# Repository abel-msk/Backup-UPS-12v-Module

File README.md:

# Backup UPS 12V Module

English | [Русский](readme.ru.md)

No-break switchover between a 12 V PSU and a 3S2P battery, with load current up to 8 A. Board size,
mounting holes and connectors J1, J4, J6, J7, J8 match the Backup power switch 12v Module.

## Background

This board is the next step of the [Backup power switch 12v Module](https://github.com/abel-msk/Backup-power-switch-12v-Module) project (v5.0). It keeps the board outline and the main connectors, but the switchover and the charger were redesigned because of the limitations found in v5.0:

| | Backup power switch v5.0 | Why it was changed | This board |
|---|---|---|---|
| **Switchover** | Relay K1 controlled by ESP32-C3 firmware, diode-OR D7 holds the outputs while the relay moves | Backup depended on running firmware, and the relay is a mechanical part in the 12 V path | Two ideal diodes and no relay. The battery leg is enabled by hardware, without firmware |
| **Mains loss detection** | Firmware compares INA219 currents | The battery back-feeds the PSU side through D7 and K1, so the PSU voltage divider still reads close to normal | U1 blocks back-feed, and the U7 detector measures PSU_IN directly |
| **Charging** | CN3763 buck charger fed directly from the PSU | With a 12.6 V PSU the pack reaches only about 11.2–11.4 V (45–55 % capacity), DONE is never asserted and most BMS boards do not balance | MT3608 boosts the charger input to 14.7 V, so the pack can charge to 12.6 V |
| **Monitoring** | Two INA219 sensors and ADC dividers | No longer needed to detect mains loss | Mains loss is detected in hardware, without a sensor. U8 (INA226) on shunt R29 measures the output current and voltage for monitoring only. The ESP32-C3 also reads ON_BATTERY, CHRG_SIG and DONE_SIG |

This design has not been tested on hardware yet.

## How it works

- **PSU to output:** ideal diode U1 (LM74700-Q1) + Q1 (AOD514).
- **Battery to output:** U2 + Q2. While mains is present, Q3 holds the EN pin of U2 low, so the battery does not discharge.
- **Mains detector:** reference U7 (LMV431AIMF) and switch Q10 (AO3401A) drive the bases of Q3 and Q7. The threshold is set with RV1.
- **Mains lost:** current immediately flows through the body diode of Q2, then U2 turns Q2 on. The output does not drop out.
- **Charging:** the MT3608 boosts PSU_IN to 14.7 V, and the CN3763 charges the pack to 12.6 V at 0.8 A.
  Without the boost, a buck charger running from 12 V cannot fully charge a 3S pack (see the README of the old board).

## Switchover logic

The thresholds and timings below come from calculation and ngspice simulation. They have not been measured on hardware.

The power path is two ideal diodes feeding the common node VOR. The no-break behavior comes from the body diode of Q2: it is permanently connected from the battery to VOR and starts conducting on its own, with no control signal. The detector only decides when to turn Q2 fully on.

### How the detector works

U7 compares the voltage on REF with its internal 1.24 V reference. REF receives a fraction of PSU_IN through the divider R20 + RV1 (upper leg) and R21 (lower leg).

| PSU_IN | U7 | Q10 | Q3 and Q7 | BAT_EN (U2 EN input) | Q2 | ON_BATTERY |
|---|---|---|---|---|---|---|
| above threshold | conducting | on | on | about 0 V | off, only the body diode conducts | 0 |
| below threshold | off | off | off | pulled up through R3 from SW_ON | on | 1 |

When PSU_IN is above the threshold, U7 pulls the gate of Q10 down through R24. Q10 turns on and feeds the bases of Q3 and Q7 through R1. When PSU_IN is below the threshold, R23 turns Q10 off and R2 discharges the bases.

### Why there are two thresholds

Without hysteresis, the detector would chatter around the threshold because of ripple on PSU_IN. The hysteresis comes from R22 (10 MΩ) between the drain of Q10 and REF:

- **Q10 on (mains present):** R22 is in parallel with the upper leg and raises REF slightly. PSU_IN has to fall further before U7 turns off. This is the battery enable threshold: `1.24 × (1 + (R20 + RV1) ∥ R22 / R21)`.
- **Q10 off (running on battery):** R22, through R1, loads the lower leg and lowers REF slightly. PSU_IN has to rise further before U7 turns on. This is the battery disable threshold: `1.24 × (1 + (R20 + RV1) / (R21 ∥ (R22 + R1)))`.

Temperature from 0 to 60 °C shifts the threshold by about ±0.02 V, because the threshold is set by the U7 reference and not by a transistor base-emitter voltage.

| RV1 | Battery enabled when PSU_IN falls below | Battery disabled when PSU_IN rises above |
|---|---|---|
| 0 Ω | 10.96 V | 11.15 V |
| 5 kΩ | 11.26 V | 11.46 V |
| 10 kΩ | 11.56 V | 11.77 V |

With tolerances (Vref ±1%, R20 and R21 ±1%, RV1 ±10%, others ±5%, 0–60 °C):

| RV1 | Battery enable | Battery disable |
|---|---|---|
| 0 Ω | 10.72–11.18 V | 10.92–11.38 V |
| 10 kΩ | 11.31–11.87 V | 11.52–12.09 V |

Hysteresis is 0.18–0.23 V. Turning RV1 clockwise raises the threshold (per the Bourns 3296 datasheet; confirm on the Baoter part with a continuity check).

### Mains lost

1. PSU_IN falls and VOR falls with it. C5 supplies part of the current.
2. As soon as VOR is above PSU_IN, U1 turns Q1 off. The battery does not back-feed the PSU or the MT3608.
3. When VOR drops about 0.8 V below the pack voltage, the body diode of Q2 starts conducting. From this point the battery supplies the load.
4. PSU_IN crosses the battery enable threshold. U7, Q10, Q3 and Q7 turn off.
5. About 60–80 µs after the threshold crossing, BAT_EN rises through R3. U2 turns Q2 on, and the drop falls from 0.8 V to a fraction of a volt.
6. ON_BATTERY goes to 1, and D4 and the external BAT LED on J12 light up.

The duration of steps 3–5 depends on how fast PSU_IN decays. If the pack is discharged so far that its voltage minus 0.8 V is below the threshold, the detector acts before the diode conducts and this phase does not occur.

### Mains restored

1. PSU_IN rises and crosses the battery disable threshold. U7 and Q10 turn on, Q3 pulls BAT_EN to ground in about 9 µs, and Q2 turns off. The load stays on the body diode of Q2.
2. When PSU_IN exceeds VOR, U1 turns Q1 on and the load moves to mains with no break.
3. ON_BATTERY returns to 0, and the CN3763 charges the pack again.

### Short dips

C3 and R2, together with the switching delay, reject short disturbances. The detector ignores a PSU_IN dip from 12.6 to 9 V lasting up to 50 µs, and a dip of 100 µs or longer enables the battery. When that happens the battery simply picks up the load.

### Output switch

The BAT_EN pull-up comes from SW_ON, so with J10 open U2 stays disabled regardless of the detector. Q5 then disconnects the output, and the ESP32 and the indicators turn off along with VOUT.

### Limitations

- **Sustained PSU sag.** If PSU_IN stays between the threshold and the pack voltage minus 0.8 V (full pack: from the threshold up to 11.8 V), the battery is not yet enabled, but current flows through the body diode of Q2. That is about 6.4 W at 8 A, so this state must not be sustained.
- **PSU voltage.** The battery disable threshold must be at least 0.3 V below PSU_IN under load. Do not use the top position of RV1 with a 12.0 V PSU.
- **Full pack with a 12.0 V PSU.** The body diode of Q2 is close to conducting, so the battery can discharge slightly. Set the PSU to 12.3–12.6 V.

## Schematic sheets

| Sheet | File | Contents | Connections to root |
|---|---|---|---|
| Root | `Backup UPS 12v Module.kicad_sch` | ideal diodes, output switch, ESP32, status transistors Q8 and Q9, indicators, J11 and J12 | |
| Boost | `boost.kicad_sch` | MT3608 (U3) and its components | PSU_IN, V15 |
| Charger | `charger.kicad_sch` | CN3763 (U4) and its components | V15, BAT+, CHRG, DONE |
| Detector | `detector.kicad_sch` | mains detector: threshold (U7, RV1, R20–R22), Q10, Q3, Q7 | PSU_IN, SW_ON, 3V3, BAT_EN, ON_BATTERY |

## ESP32-C3 Pro Mini

3.3 V comes from an AMS1117-3.3 (U6) fed by VOUT, so the ESP turns off when the output is switched off.

| GPIO | Signal | Meaning |
|---|---|---|
| GPIO4 | ON_BATTERY | 1 on battery, 0 on mains. Interrupt on both edges = switchover moment |
| GPIO3 | CHRG_SIG | 1 charging. Enable the internal pull-up |
| GPIO7 | DONE_SIG | 1 charge complete. Enable the internal pull-up |
| GPIO8 | SDA | I2C data to INA226 (U8, address 0x40), 10 kΩ pull-up on the board |
| GPIO9 | SCL | I2C clock to INA226 |

CHRG_SIG and DONE_SIG pass through 2N7002 transistors (Q8, Q9), so the logic is inverted. If V15 is present but the CN3763 is not charging, both signals read 0. Without mains both read 1, so check ON_BATTERY first. U6 dissipates about 0.9 W at 100 mA with 12.6 V input.

Charge status LEDs connect to J11 (JST PH, 4 pins): 1 CHRG anode, 2 CHRG cathode,
3 DONE anode, 4 DONE cathode. The current-limiting resistors are on the board.

Load power indicator: green D5 from VOUT through R27 3 kΩ, lit when voltage is present on the output (marked OUT). A matching external LED connects to J12 (JST PH, 4 pins): pin 1 anode, pin 2 cathode, through R28 3 kΩ from VOUT.

Battery operation indicator: D4 on the board and an external LED on J12 (pin 3 anode, pin 4 cathode). Both light when ON_BATTERY = 1, through switch Q11 (2N7002), powered from VOUT through R25 and R26 at 3 kΩ each, about 3 mA per LED. The indicator does not work when the output is off. Board markings: J11 C+ C- D+ D- (C = CHRG, D = DONE), J12 left to right +OUT- and +BAT-.

Output monitor: U8 (INA226) measures the output current on shunt R29 (2 mΩ, 2512) and the output voltage after the shunt. At 8 A the shunt drops 16 mV and dissipates 0.13 W. The ESP32 and U6 are fed before the shunt, so their current is not counted. ALERT is not connected.

Display connector J13 with SPI and I2C (JST PH, 8 pins):

| Pin | Signal | ESP32 |
|---|---|---|
| 1 | GND | |
| 2 | 3V3 | from U6 |
| 3 | SCK | GPIO6 |
| 4 | MOSI | GPIO10 |
| 5 | MISO | GPIO21 |
| 6 | CS | GPIO1 |
| 7 | SDA | GPIO8 |
| 8 | SCL | GPIO9 |

## Output off

An external switch connects to J10 (JST PH, 2 pins, no polarity).
Closed: output on. Open or not connected: output off.

- Q5 (AOD403) breaks the positive output line, and R16 discharges the output when there is no load.
- With no mains and the output off, the battery typically supplies about 11 µA to the board, about 17 µA maximum (CN3763 9–15 µA, U2 in shutdown up to 1.5 µA).
- With mains present, the battery keeps charging even when the output is off.
- F1 (1808 fuse, 10 A, in a 01550900M style SMD holder) sits between Q5 and VOUT. At 8 A continuous it runs at 80% of its rating, so a hot board can blow it early. Do not fit a fuse above 10 A: the original holder is rated for 10 A.
- J3 (JST XH) is limited to 3 A. The main 8 A current flows through power connectors J4, J6, J7, J8.

## Requirements

- PSU 12–12.6 V, at least 10 A (8 A load + about 1.1 A charger). PSU_IN under load must stay above the battery disable threshold, otherwise the board switches to battery.
- 3S BMS rated for at least 15 A continuous. Discharge cutoff is handled only by the BMS.
- On battery, the output equals the pack voltage minus about 0.1 V: from 12.6 V down to about 9 V.
- Routing (IPC-2221, 35 µm copper, up to 20 °C rise): PSU_IN and GNDPWR 4.5 mm, VOUT, VOR and BAT+ 4.0 mm,
  charger nets 0.8 mm, signal nets 0.2 mm. GNDPWR is best as a polygon. Widths are set in the project net classes.
- Vias 0.6 / 0.3 mm, each carries about 1.9 A: use at least 5 on a power net, preferably 8.

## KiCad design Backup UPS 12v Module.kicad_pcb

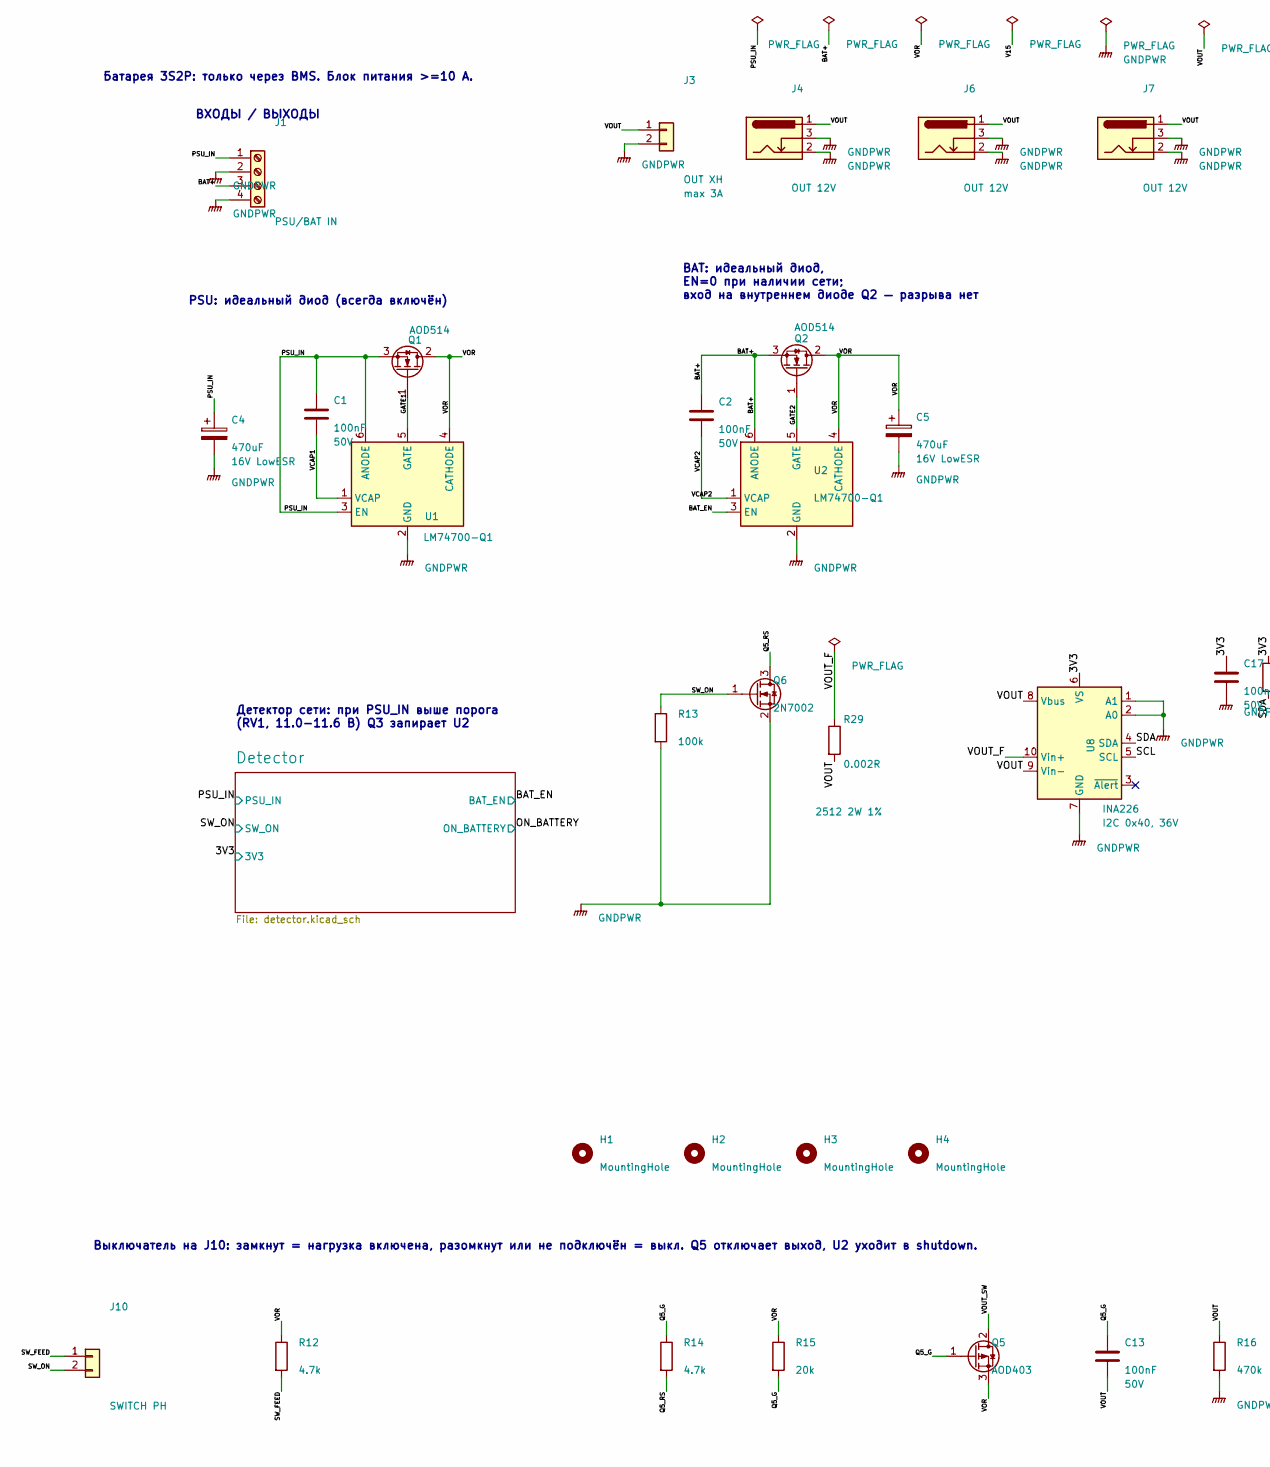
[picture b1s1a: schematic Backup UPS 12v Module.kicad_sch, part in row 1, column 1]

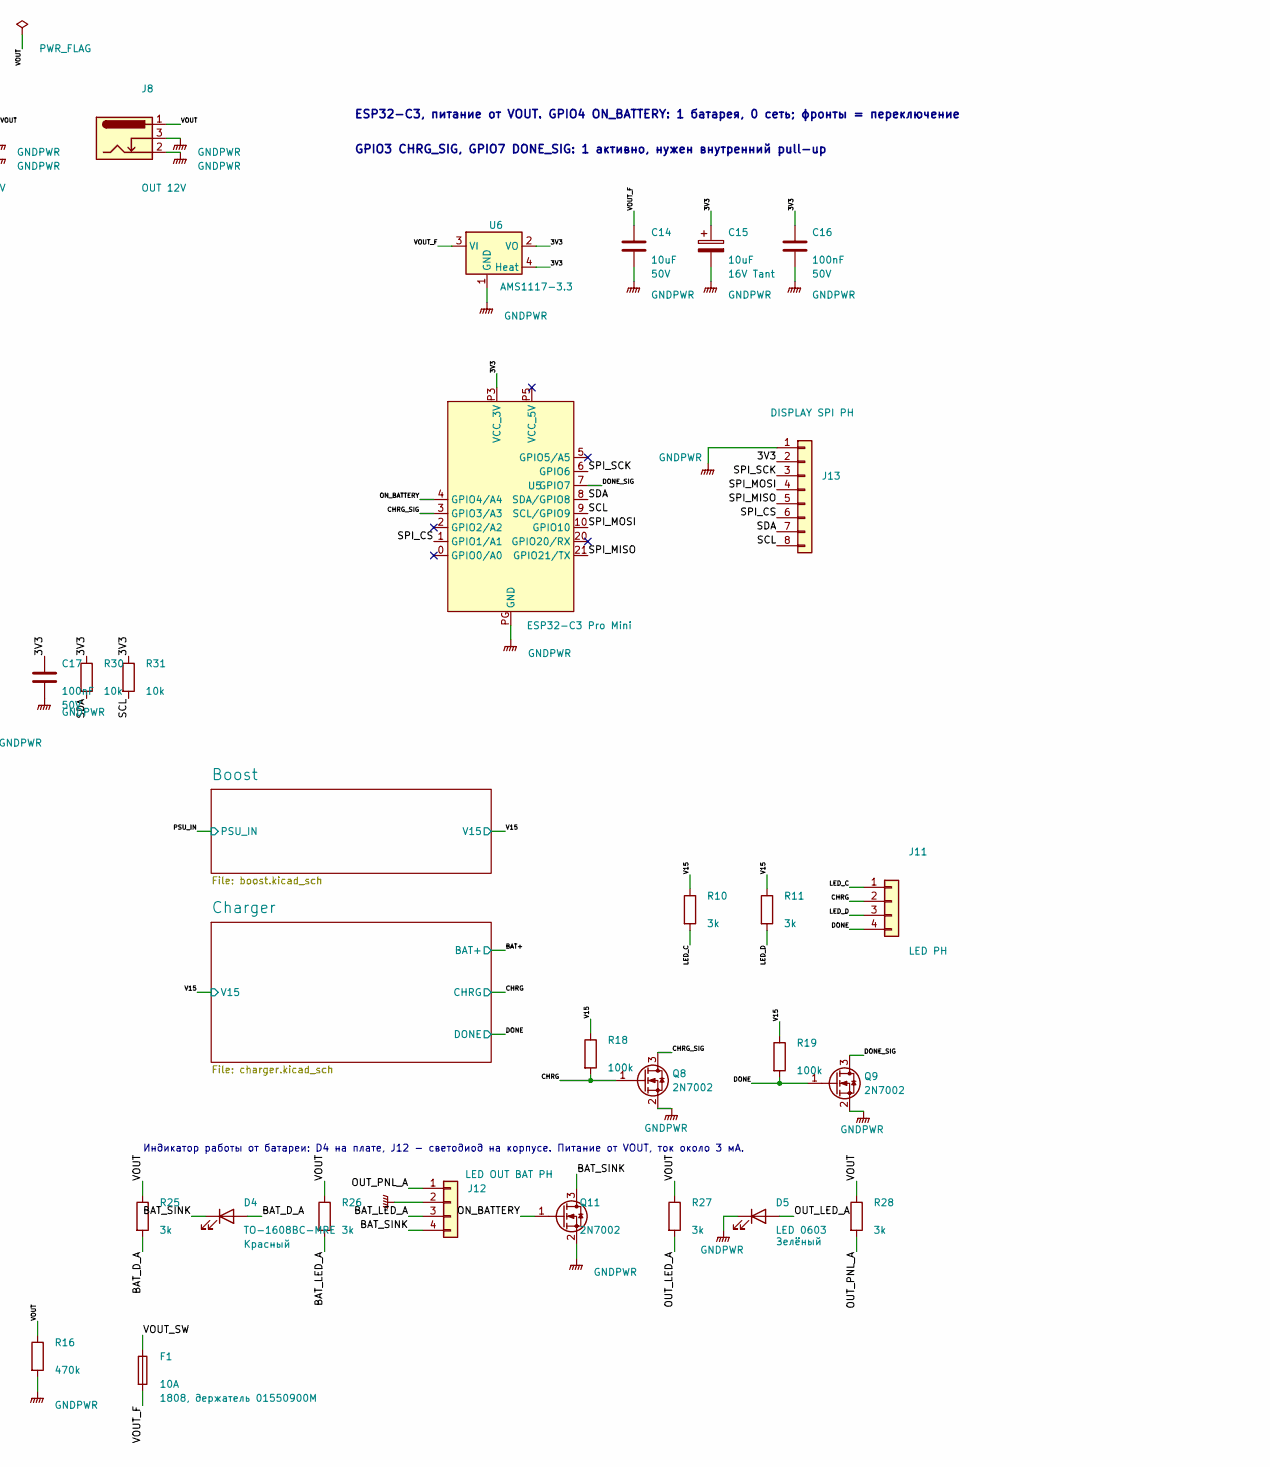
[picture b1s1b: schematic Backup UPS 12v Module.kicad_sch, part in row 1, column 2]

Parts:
C1, C2, C13, C16, C17: 100nF; C_0805_2012Metric
C4, C5: 470uF; CP_Radial_D8.0mm_P3.50mm
C14: 10uF; C_1206_3216Metric
C15: 10uF; CP_EIA-3216-18_Kemet-A
D4: TO-1608BC-MRE; LED_0603_1608Metric; MPN TO-1608BC-MRE
D5: LED 0603; LED_0603_1608Metric
F1: 10A; Fuseholder_1808_SMD_Littelfuse_01550900; MPN 01550900M + 0451010
H1, H2, H3, H4: MountingHole; MountingHole_3.5mm_Pad_TopBottom
J1: PSU/BAT IN; ScrewTerminal_HB762_7.62_4P
J3: OUT XH; JST_XH_B2B-XH-A_1x02_P2.50mm_Vertical; MPN B2B-XH-A
J4, J6, J7, J8: OUT 12V; BarrelJack_Horizontal
J10: SWITCH PH; JST_PH_B2B-PH-K_1x02_P2.00mm_Vertical; MPN B2B-PH-K
J11: LED PH; JST_PH_B4B-PH-K_1x04_P2.00mm_Vertical; MPN B4B-PH-K
J12: LED OUT BAT PH; JST_PH_B4B-PH-K_1x04_P2.00mm_Vertical
J13: DISPLAY SPI PH; JST_PH_B8B-PH-K_1x08_P2.00mm_Vertical
Q1, Q2: AOD514; TO-252-2; MPN AOD514
Q5: AOD403; TO-252-2; MPN AOD403
Q6, Q8, Q9, Q11: 2N7002; SOT-23; MPN 2N7002LT1G
R10, R11, R25, R26, R27, R28: 3k; R_0603_1608Metric
R12, R14: 4.7k; R_0603_1608Metric
R13, R18, R19: 100k; R_0805_2012Metric
R15: 20k; R_0603_1608Metric
R16: 470k; R_0805_2012Metric
R29: 0.002R; R_2512_6332Metric_Pad1.40x3.35mm_HandSolder
R30, R31: 10k; R_0805_2012Metric
U1, U2: LM74700-Q1; SOT-23-6; MPN LM74700QDBVRQ1
U5: ESP32-C3 Pro Mini; ESP32-C3_Pro_mini_pin
U6: AMS1117-3.3; SOT-223; MPN AMS1117-3.3
U8: INA226; TSSOP-10_3x3mm_P0.5mm; MPN INA226AIDGSR

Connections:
/3V3: C15.1, C16.1, C17.1, J13.2, R30.1, R31.1, U5.P3 (VCC_3V), U6.2 (VO), U6.4 (Heat), U8.6 (VS); also elsewhere on the board
/BAT+: C2.1, J1.3, Q2.3 (S), U2.6 (ANODE); also elsewhere on the board
/BAT_D_A: D4.2 (A), R25.2
/BAT_EN: U2.3 (EN); also elsewhere on the board
/BAT_LED_A: J12.3, R26.2
/BAT_SINK: D4.1 (K), J12.4, Q11.3 (D)
/CHRG: J11.2, Q8.1 (G), R18.2; also elsewhere on the board
/CHRG_SIG: Q8.3 (D), U5.3 (GPIO3/A3)
/DONE: J11.4, Q9.1 (G), R19.2; also elsewhere on the board
/DONE_SIG: Q9.3 (D), U5.7 (GPIO7)
/GATE1: Q1.1 (G), U1.5 (GATE)
/GATE2: Q2.1 (G), U2.5 (GATE)
/LED_C: J11.1, R10.2
/LED_D: J11.3, R11.2
/ON_BATTERY: Q11.1 (G), U5.4 (GPIO4/A4); also elsewhere on the board
/OUT_LED_A: D5.2 (A), R27.2
/OUT_PNL_A: J12.1, R28.2
/PSU_IN: C1.1, C4.1, J1.1, Q1.3 (S), U1.3 (EN), U1.6 (ANODE); also elsewhere on the board
/Q5_G: C13.1, Q5.1 (G), R14.1, R15.2
/Q5_RS: Q6.3 (D), R14.2
/SCL: J13.8, R31.2, U5.9 (SCL/GPIO9), U8.5 (SCL)
/SDA: J13.7, R30.2, U5.8 (SDA/GPIO8), U8.4 (SDA)
/SPI_CS: J13.6, U5.1 (GPIO1/A1)
/SPI_MISO: J13.5, U5.21 (GPIO21/TX)
/SPI_MOSI: J13.4, U5.10 (GPIO10)
/SPI_SCK: J13.3, U5.6 (GPIO6)
/SW_FEED: J10.1, R12.2
/SW_ON: J10.2, Q6.1 (G), R13.1; also elsewhere on the board
/V15: R10.1, R11.1, R18.1, R19.1; also elsewhere on the board
/VCAP1: C1.2, U1.1 (VCAP)
/VCAP2: C2.2, U2.1 (VCAP)
/VOR: C5.1, Q1.2 (D), Q2.2 (D), Q5.3 (S), R12.1, R15.1, U1.4 (CATHODE), U2.4 (CATHODE)
/VOUT: C13.2, J3.1, J4.1, J6.1, J7.1, J8.1, R16.1, R25.1, R26.1, R27.1, R28.1, R29.2, U8.8 (Vbus), U8.9 (Vin-)
/VOUT_F: C14.1, F1.2, R29.1, U6.3 (VI), U8.10 (Vin+)
/VOUT_SW: F1.1, Q5.2 (D)
GNDPWR: C4.2, C5.2, C14.2, C15.2, C16.2, C17.2, D5.1 (K), J1.2, J1.4, J3.2, J4.2, J4.3, J6.2, J6.3, J7.2, J7.3, J8.2, J8.3, J12.2, J13.1, Q6.2 (S), Q8.2 (S), Q9.2 (S), Q11.2 (S), R13.2, R16.2, U1.2 (GND), U2.2 (GND), U5.PG (GND), U6.1 (GND), U8.1 (A1), U8.2 (A0), U8.7 (GND); also elsewhere on the board

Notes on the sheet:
BAT: идеальный диод, EN=0 при наличии сети; вход на внутреннем диоде Q2 — разрыва нет
ВХОДЫ / ВЫХОДЫ
Индикатор работы от батареи: D4 на плате, J12 - светодиод на корпусе. Питание от VOUT, ток около 3 мА.
Батарея 3S2P: только через BMS. Блок питания >=10 А.
PSU: идеальный диод (всегда включён)
Выключатель на J10: замкнут = нагрузка включена, разомкнут или не подключён = выкл. Q5 отключает выход, U2 уходит в shutdown.
ESP32-C3, питание от VOUT. GPIO4 ON_BATTERY: 1 батарея, 0 сеть; фронты = переключение
Детектор сети: при PSU_IN выше порога (RV1, 11.0-11.6 В) Q3 запирает U2
GPIO3 CHRG_SIG, GPIO7 DONE_SIG: 1 активно, нужен внутренний pull-up

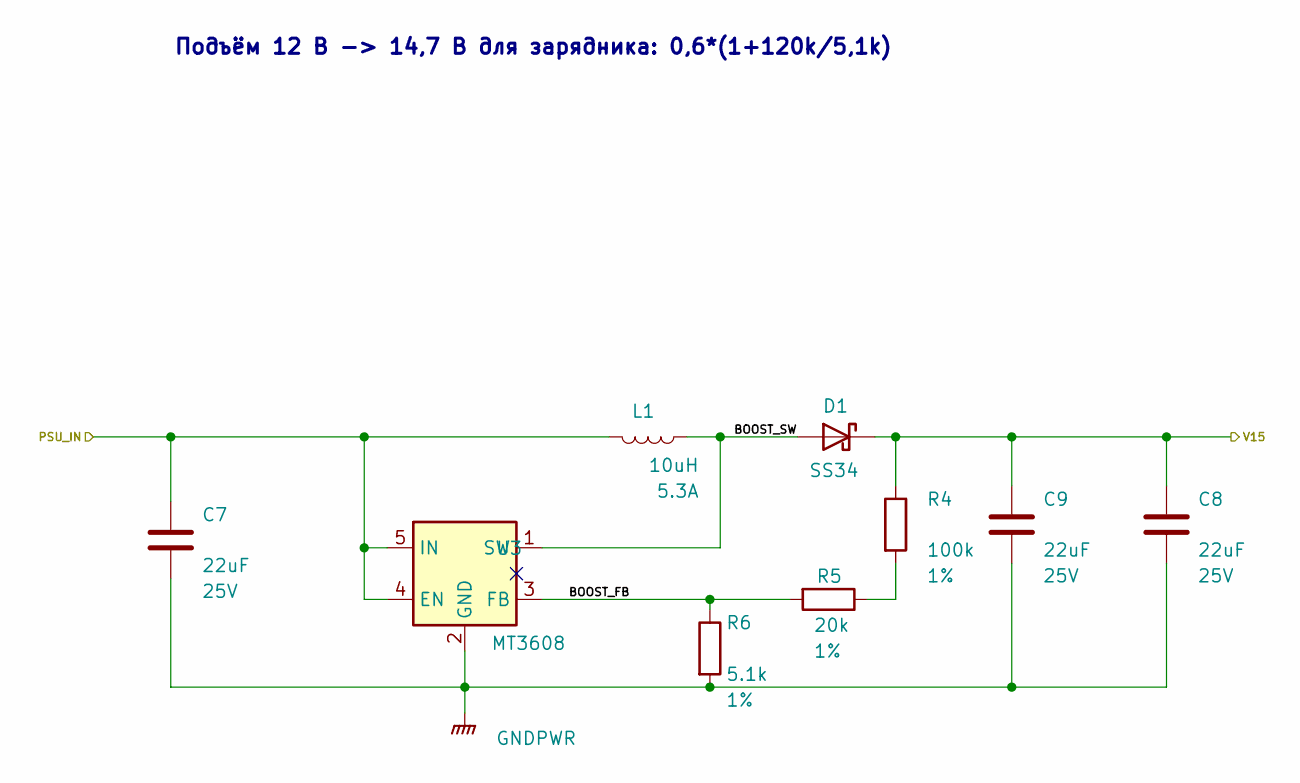
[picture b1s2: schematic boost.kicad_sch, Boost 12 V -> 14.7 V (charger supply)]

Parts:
C7, C8, C9: 22uF; C_1206_3216Metric
D1: SS34; D_SMA; MPN SS34
L1: 10uH; L_Molded_0650_7.5x6.6_H5.0
R4: 100k; R_0805_2012Metric
R5: 20k; R_0805_2012Metric
R6: 5.1k; R_0805_2012Metric
U3: MT3608; SOT-23-6; MPN MT3608

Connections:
/Boost/BOOST_FB: R5.2, R6.1, U3.3 (FB)
/Boost/BOOST_SW: D1.2 (A), L1.2, U3.1 (SW)
/PSU_IN: C7.1, L1.1, U3.4 (EN), U3.5 (IN); also elsewhere on the board
/V15: C8.1, C9.1, D1.1 (K), R4.1; also elsewhere on the board
GNDPWR: C7.2, C8.2, C9.2, R6.2, U3.2 (GND); also elsewhere on the board
unnamed: R4.2, R5.1

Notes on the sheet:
Подъём 12 В -> 14,7 В для зарядника: 0,6*(1+120k/5,1k)

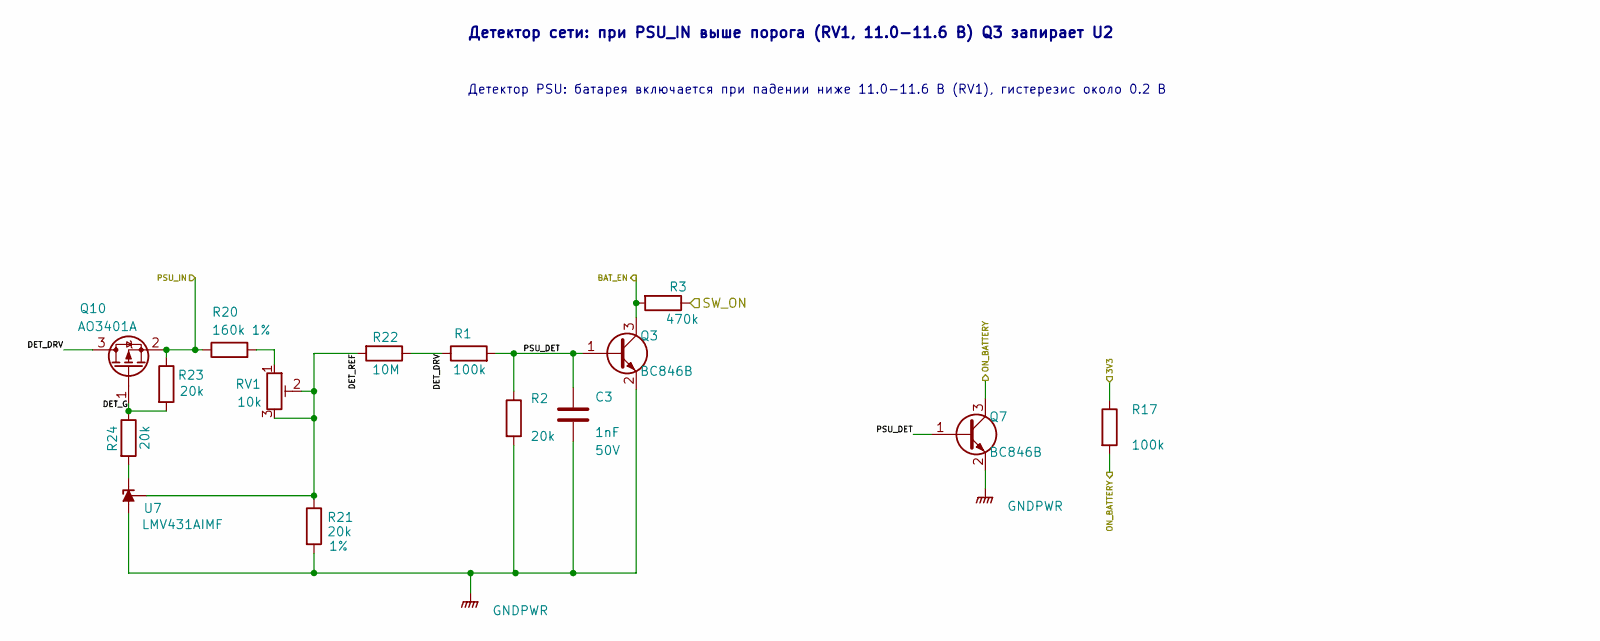
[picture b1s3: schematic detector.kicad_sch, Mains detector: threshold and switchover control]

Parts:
C3: 1nF; C_0603_1608Metric
Q3, Q7: BC846B; SOT-23; MPN BC846B
Q10: AO3401A; SOT-23; MPN AO3401A
R1, R17: 100k; R_0805_2012Metric
R2, R24: 20k; R_0603_1608Metric
R3: 470k; R_0805_2012Metric
R20: 160k; R_0805_2012Metric
R21: 20k; R_0805_2012Metric
R22: 10M; R_0805_2012Metric_Pad1.20x1.40mm_HandSolder
R23: 20k; R_0805_2012Metric_Pad1.20x1.40mm_HandSolder
RV1: 10k; Potentiometer_Bourns_3296W_Vertical; MPN 3296W-103
U7: LMV431AIMF; SOT-23; MPN LMV431AIMF

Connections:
/3V3: R17.1; also elsewhere on the board
/BAT_EN: Q3.3 (C), R3.2; also elsewhere on the board
/Detector/DET_DRV: Q10.3 (D), R1.1, R22.1
/Detector/DET_G: Q10.1 (G), R23.2, R24.1
/Detector/DET_REF: R21.1, R22.2, RV1.2, RV1.3, U7.1 (REF)
/Detector/PSU_DET: C3.1, Q3.1 (B), Q7.1 (B), R1.2, R2.1
/ON_BATTERY: Q7.3 (C), R17.2; also elsewhere on the board
/PSU_IN: Q10.2 (S), R20.1, R23.1; also elsewhere on the board
/SW_ON: R3.1; also elsewhere on the board
GNDPWR: C3.2, Q3.2 (E), Q7.2 (E), R2.2, R21.2, U7.3 (A); also elsewhere on the board
unnamed: R20.2, RV1.1
unnamed: R24.2, U7.2 (K)

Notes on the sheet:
Детектор сети: при PSU_IN выше порога (RV1, 11.0-11.6 В) Q3 запирает U2
Детектор PSU: батарея включается при падении ниже 11.0-11.6 В (RV1), гистерезис около 0.2 В

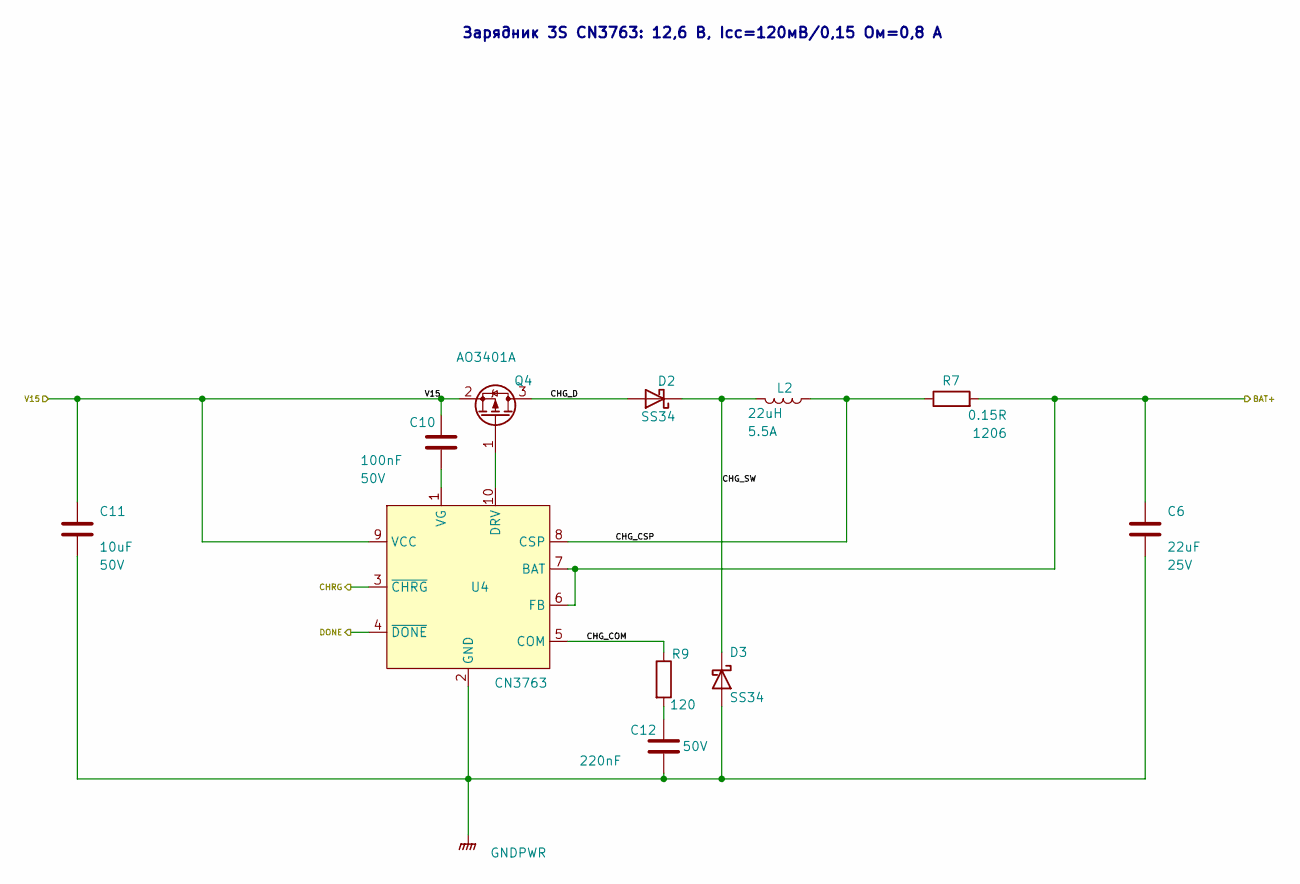
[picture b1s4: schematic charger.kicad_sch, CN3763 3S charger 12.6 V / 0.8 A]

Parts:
C6: 22uF; C_1206_3216Metric
C10: 100nF; C_0805_2012Metric
C11: 10uF; C_1206_3216Metric
C12: 220nF; C_0805_2012Metric
D2, D3: SS34; D_SMA; MPN SS34
L2: 22uH; L_Molded_1040_11.6x10.1_H4.0
Q4: AO3401A; SOT-23; MPN AO3401A
R7: 0.15R; R_1206_3216Metric
R9: 120; R_0603_1608Metric
U4: CN3763; SSOP-10_3.9x4.9mm_P1.00mm; MPN CN3763

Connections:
/BAT+: C6.1, R7.2, U4.6 (FB), U4.7 (BAT); also elsewhere on the board
/CHRG: U4.3 (~CHRG); also elsewhere on the board
/Charger/CHG_COM: R9.1, U4.5 (COM)
/Charger/CHG_CSP: L2.1, R7.1, U4.8 (CSP)
/Charger/CHG_D: D2.2 (A), Q4.3 (D)
/Charger/CHG_SW: D2.1 (K), D3.1 (K), L2.2
/DONE: U4.4 (~DONE); also elsewhere on the board
/V15: C10.1, C11.1, Q4.2 (S), U4.9 (VCC); also elsewhere on the board
GNDPWR: C6.2, C11.2, C12.2, D3.2 (A), U4.2 (GND); also elsewhere on the board
unnamed: C12.1, R9.2
unnamed: Q4.1 (G), U4.10 (DRV)
unnamed: C10.2, U4.1 (VG)

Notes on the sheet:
Зарядник 3S CN3763: 12,6 В, Icc=120мВ/0,15 Ом=0,8 А

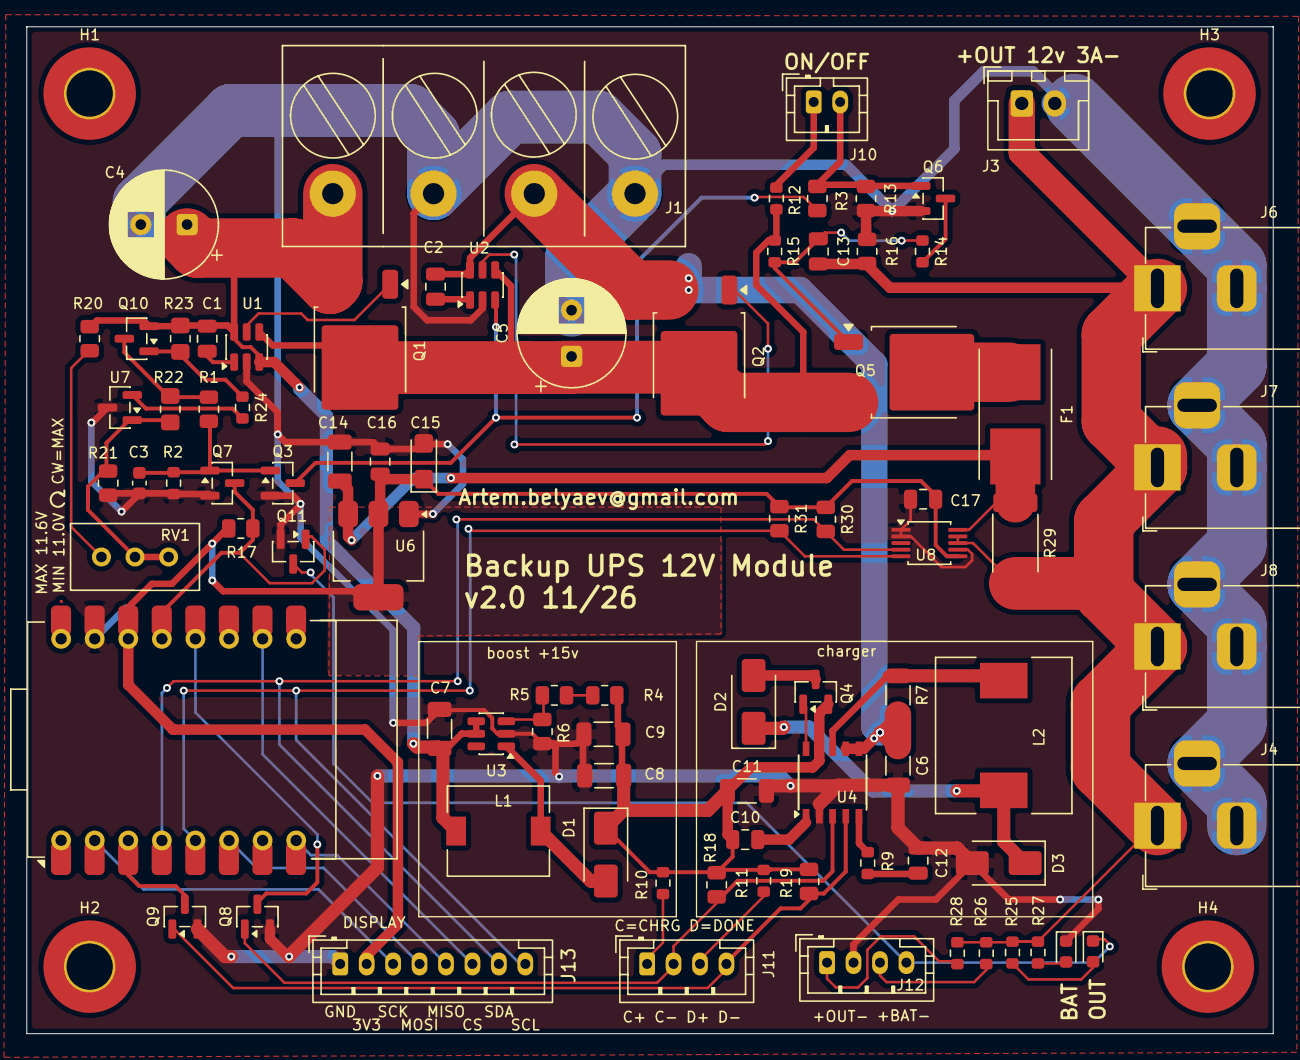
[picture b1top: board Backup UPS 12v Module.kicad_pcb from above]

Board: 2 copper layers, 94.3 x 76.2 mm, 89 parts (0 on the bottom side), 52 nets.

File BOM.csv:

Refs;Qty;Value;Footprint;Источник
J1;1;PSU/BAT IN HB762-7.62-4P;ScrewTerminal_HB762_7.62_4P;склад
J3;1;OUT XH max 3A;JST_XH_B2B-XH-A_1x02_P2.50mm_Vertical;AliExpress
J4 J6 J7 J8;4;OUT 12V;BarrelJack_Horizontal;как на старой плате
U1 U2;2;LM74700-Q1;SOT-23-6;AliExpress
Q1 Q2;2;AOD514;TO-252-2;склад
C1 C2 C10 C13 C16;5;100nF 50V;C_0805_2012Metric;склад
C4 C5;2;470uF 16V LowESR;CP_Radial_D8.0mm_P3.50mm;склад
R2 R15 R24;3;20k;R_0603_1608Metric;склад
R5;1;20k 1%;R_0805_2012Metric;AliExpress
R23;1;20k;R_0805_2012Metric_Pad1.20x1.40mm_HandSolder;склад
C3;1;1nF 50V;C_0603_1608Metric;склад
Q3 Q7;2;BC846B;SOT-23;склад
R3 R16;2;470k;R_0805_2012Metric;склад
U3;1;MT3608;SOT-23-6;склад
L1;1;10uH 5.3A;L_Molded_0650_7.5x6.6_H5.0;склад
D1 D2 D3;3;SS34;D_SMA;склад
R1 R13 R17;3;100k;R_0805_2012Metric;склад
R4;1;100k 1%;R_0805_2012Metric;склад
R6;1;5.1k 1%;R_0805_2012Metric;склад
C7 C8 C9 C6;4;22uF 25V;C_1206_3216Metric;склад
U4;1;CN3763;SSOP-10_3.9x4.9mm_P1.00mm;AliExpress
Q4 Q10;2;AO3401A;SOT-23;склад
L2;1;22uH 5.5A;L_Molded_1040_11.6x10.1_H4.0;склад
R7;1;0.15R 1206;R_1206_3216Metric;AliExpress
C11 C14;2;10uF 50V;C_1206_3216Metric;склад
R9;1;120;R_0603_1608Metric;склад
C12;1;220nF 50V;C_0805_2012Metric;AliExpress
R10 R11 R25 R26 R27 R28;6;3k;R_0603_1608Metric;склад
J10;1;SWITCH PH;JST_PH_B2B-PH-K_1x02_P2.00mm_Vertical;AliExpress
R12 R14;2;4.7k;R_0603_1608Metric;склад
R18 R19;2;100k;R_0805_2012Metric;склад
Q6 Q8 Q9 Q11;4;2N7002;SOT-23;склад
Q5;1;AOD403;TO-252-2;AliExpress
U5;1;ESP32-C3 Pro Mini;ESP32-C3_Pro_mini_pin;есть, в базе не числится
U6;1;AMS1117-3.3;SOT-223;склад
C15;1;10uF 16V Tant;CP_EIA-3216-18_Kemet-A;склад
J11;1;LED PH;JST_PH_B4B-PH-K_1x04_P2.00mm_Vertical;AliExpress
R20;1;160k 1%;R_0805_2012Metric;AliExpress
R21;1;20k 1%;R_0805_2012Metric;AliExpress
R22;1;10M;R_0805_2012Metric_Pad1.20x1.40mm_HandSolder;AliExpress
U7;1;LMV431AIMF;SOT-23;склад
RV1;1;10k 3296W-103 Baoter;Potentiometer_Bourns_3296W_Vertical;склад
D4;1;TO-1608BC-MRE красный;LED_0603_1608Metric;склад
J12;1;LED OUT BAT PH;JST_PH_B4B-PH-K_1x04_P2.00mm_Vertical;AliExpress
D5;1;LED 0603 зелёный;LED_0603_1608Metric;AliExpress
F1;1;предохранитель 1808 10A + держатель 01550900M;Fuseholder_1808_SMD_Littelfuse_01550900;AliExpress
U8;1;INA226;TSSOP-10_3x3mm_P0.5mm;AliExpress
R29;1;0.002R 2512 2W 1%;R_2512_6332Metric_Pad1.40x3.35mm_HandSolder;AliExpress
C17;1;100nF 50V;C_0805_2012Metric;склад
R30 R31;2;10k;R_0805_2012Metric;AliExpress
J13;1;DISPLAY SPI PH;JST_PH_B8B-PH-K_1x08_P2.00mm_Vertical;склад
